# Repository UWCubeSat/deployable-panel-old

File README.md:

# Deployable Solar Panel

KiCAD design files for prototype 1U solar panels.

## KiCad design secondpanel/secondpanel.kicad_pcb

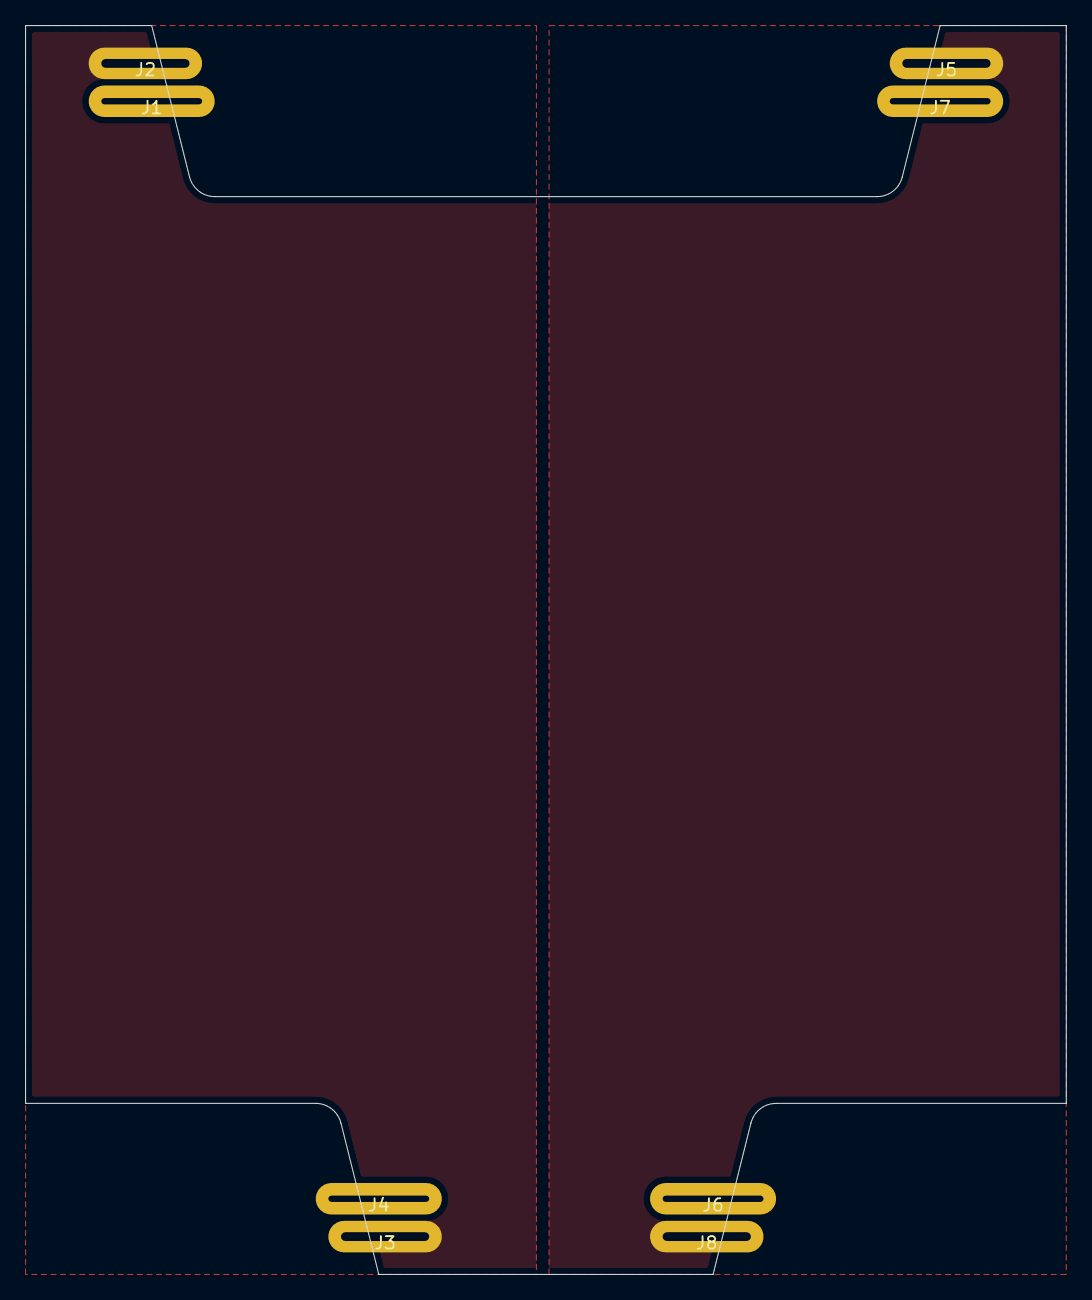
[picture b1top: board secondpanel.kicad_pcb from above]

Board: 2 copper layers, 82.5 x 99.0 mm, 8 parts (0 on the bottom side), 4 nets, no tracks yet.

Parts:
J1, J4, J6, J7: Conn_01x01_Female; hingejunct
J2, J3, J5, J8: Conn_01x01_Female; hingejunct_copy

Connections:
unnamed: J1.1, J4.1
unnamed: J2.1, J3.1
unnamed: J5.1, J8.1
unnamed: J6.1, J7.1

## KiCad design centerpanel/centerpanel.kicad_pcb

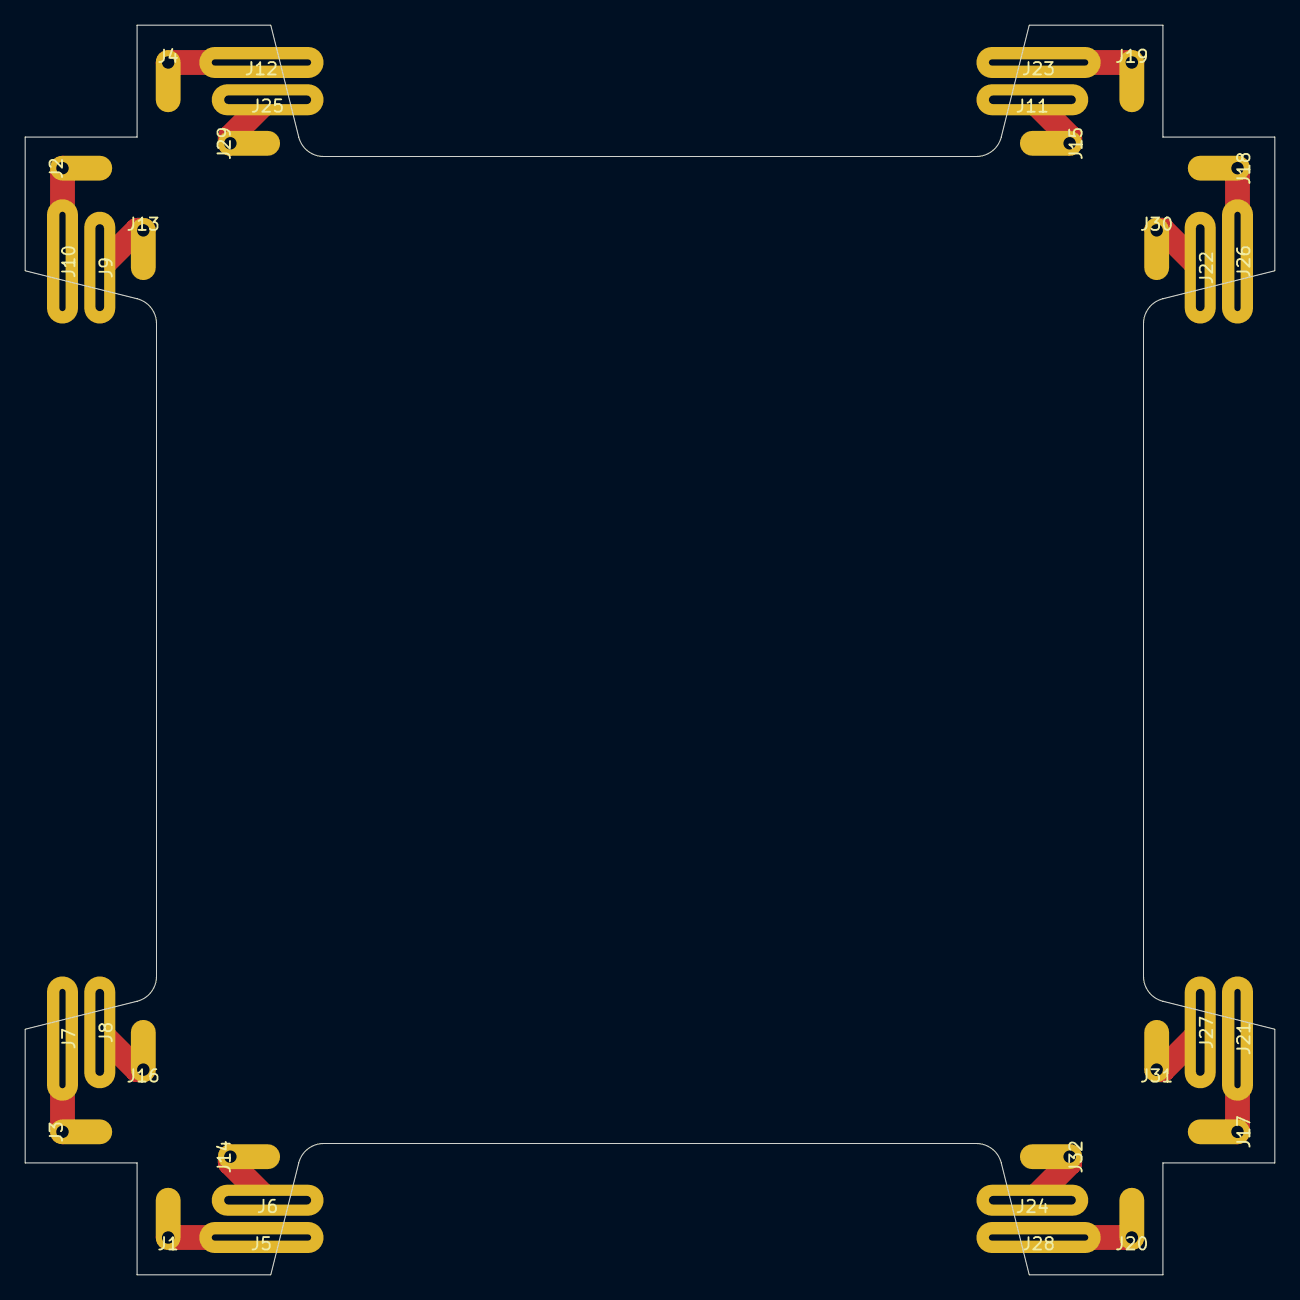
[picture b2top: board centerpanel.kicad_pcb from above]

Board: 2 copper layers, 100.5 x 100.5 mm, 32 parts (0 on the bottom side), 16 nets.

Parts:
J1, J2, J3, J4, J13, J14, J15, J16, J17, J18, J19, J20, J29, J30, J31, J32: Conn_01x01_Male; wiresolderpoint
J5, J7, J10, J12, J21, J23, J26, J28: Conn_01x01_Female; hingepoint
J6, J8, J9, J11, J22, J24, J25, J27: Conn_01x01_Female; wirepoint

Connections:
unnamed: J1.1, J5.1
unnamed: J3.1, J7.1
unnamed: J2.1, J10.1
unnamed: J11.1, J15.1
unnamed: J4.1, J12.1
unnamed: J9.1, J13.1
unnamed: J6.1, J14.1
unnamed: J8.1, J16.1
unnamed: J17.1, J21.1
unnamed: J18.1, J26.1
unnamed: J19.1, J23.1
unnamed: J20.1, J28.1
unnamed: J22.1, J30.1
unnamed: J24.1, J32.1
unnamed: J25.1, J29.1
unnamed: J27.1, J31.1

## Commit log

2021-12-17 Added prototype PCB KiCAD files.
